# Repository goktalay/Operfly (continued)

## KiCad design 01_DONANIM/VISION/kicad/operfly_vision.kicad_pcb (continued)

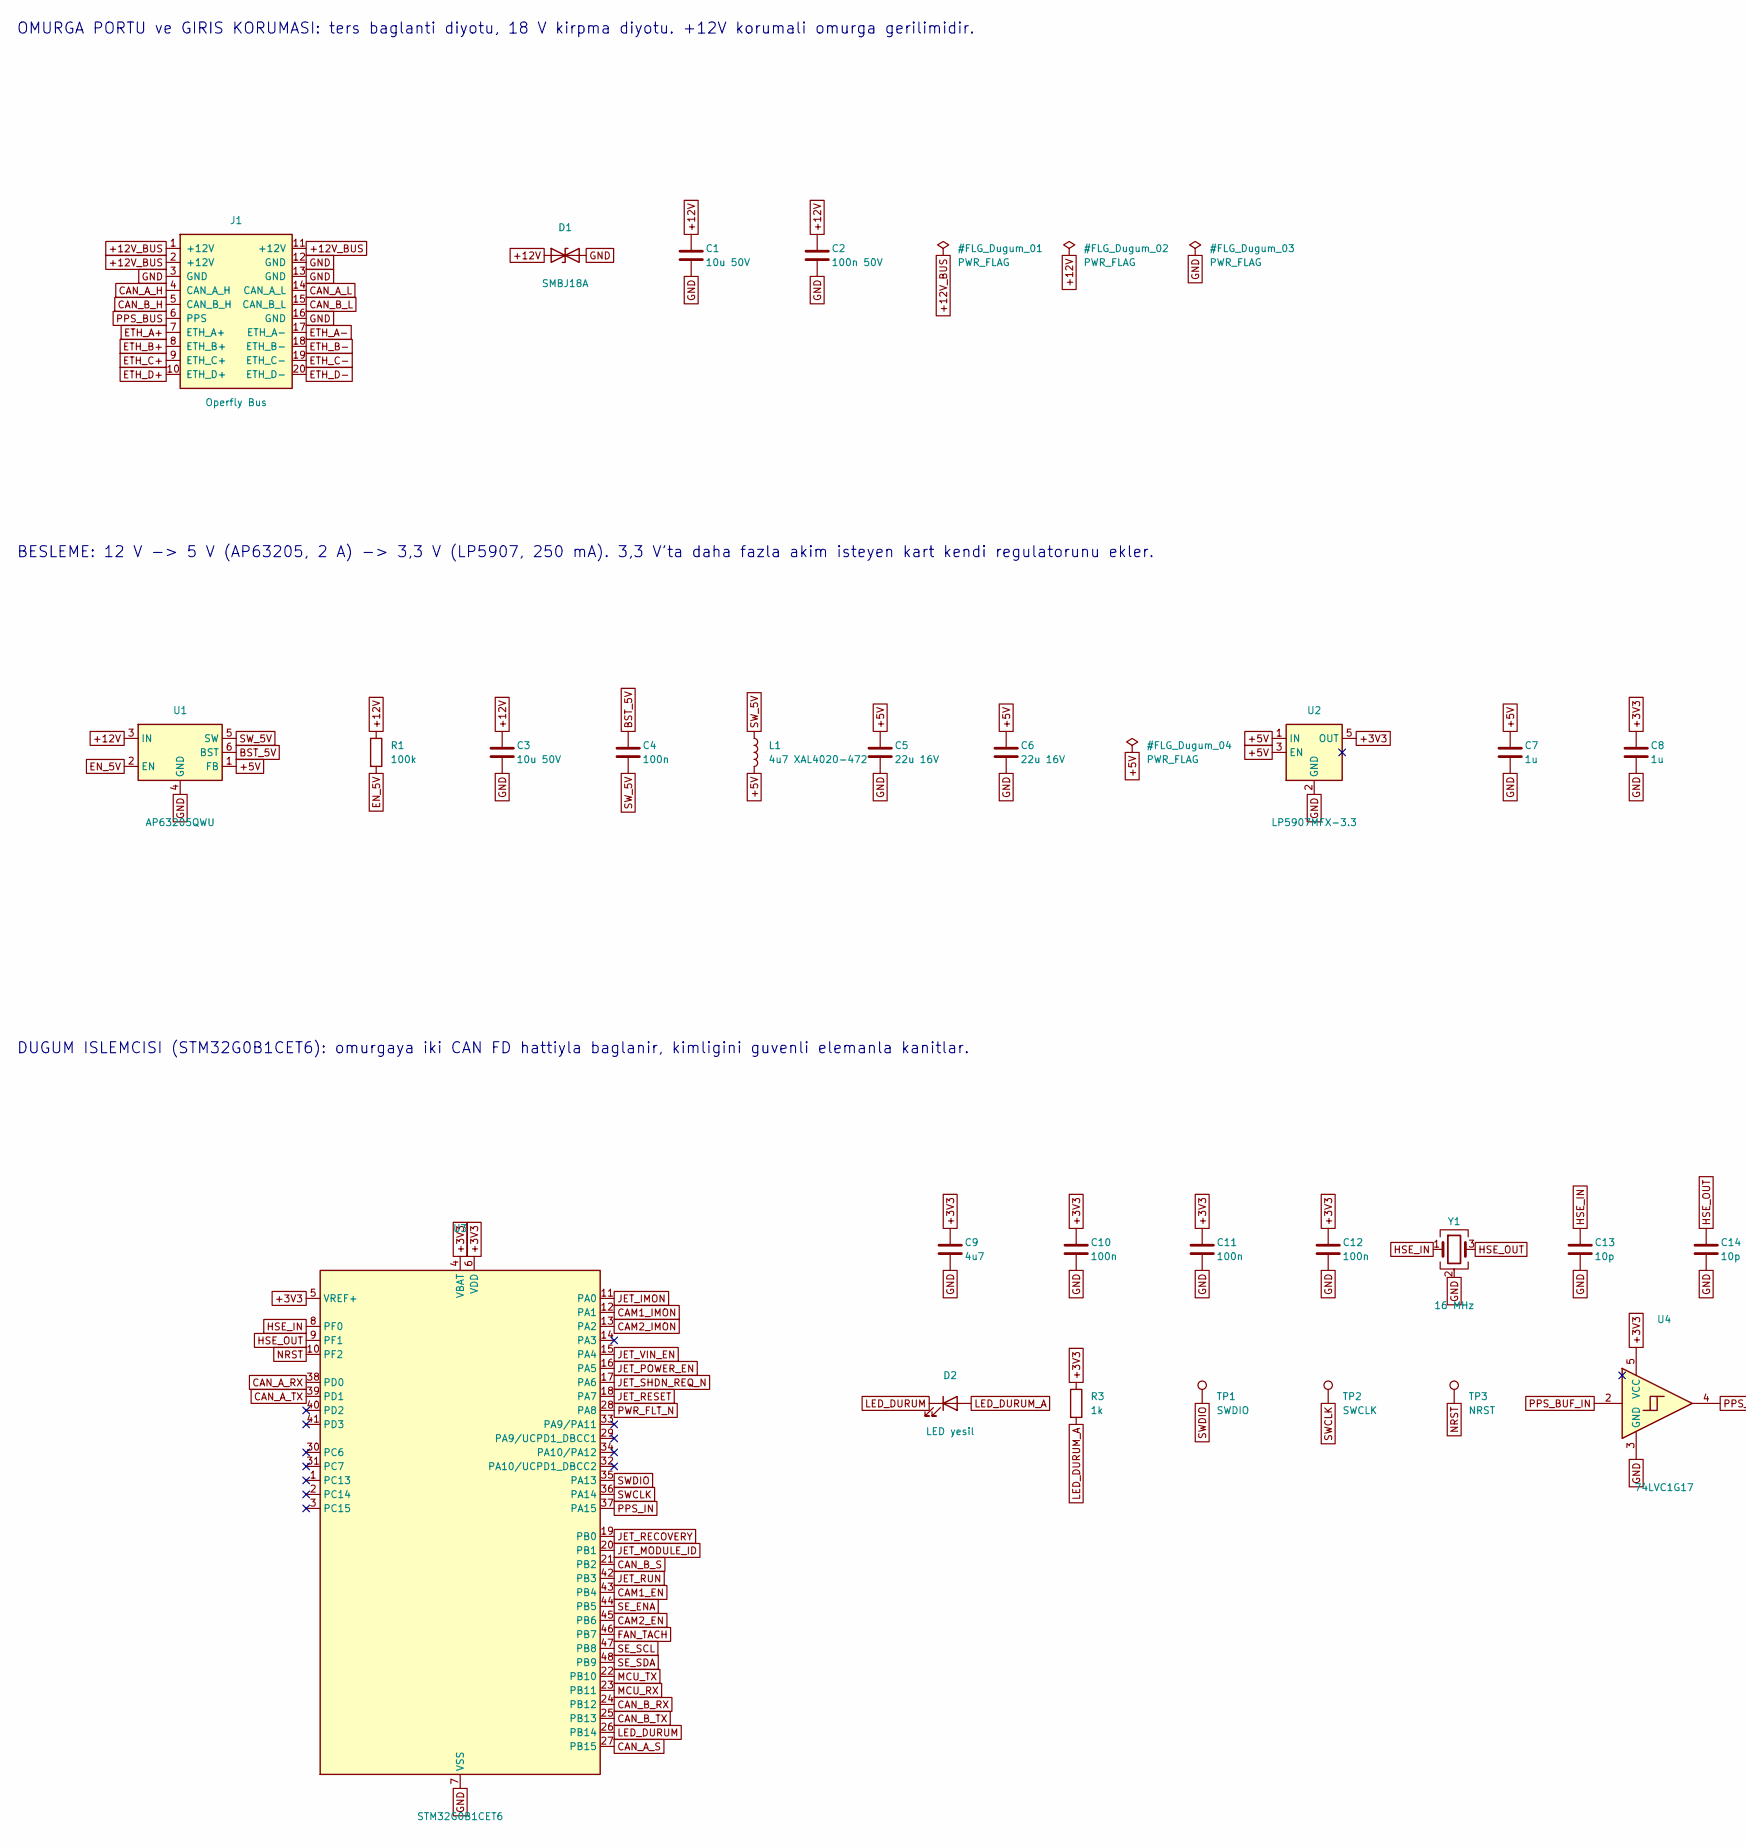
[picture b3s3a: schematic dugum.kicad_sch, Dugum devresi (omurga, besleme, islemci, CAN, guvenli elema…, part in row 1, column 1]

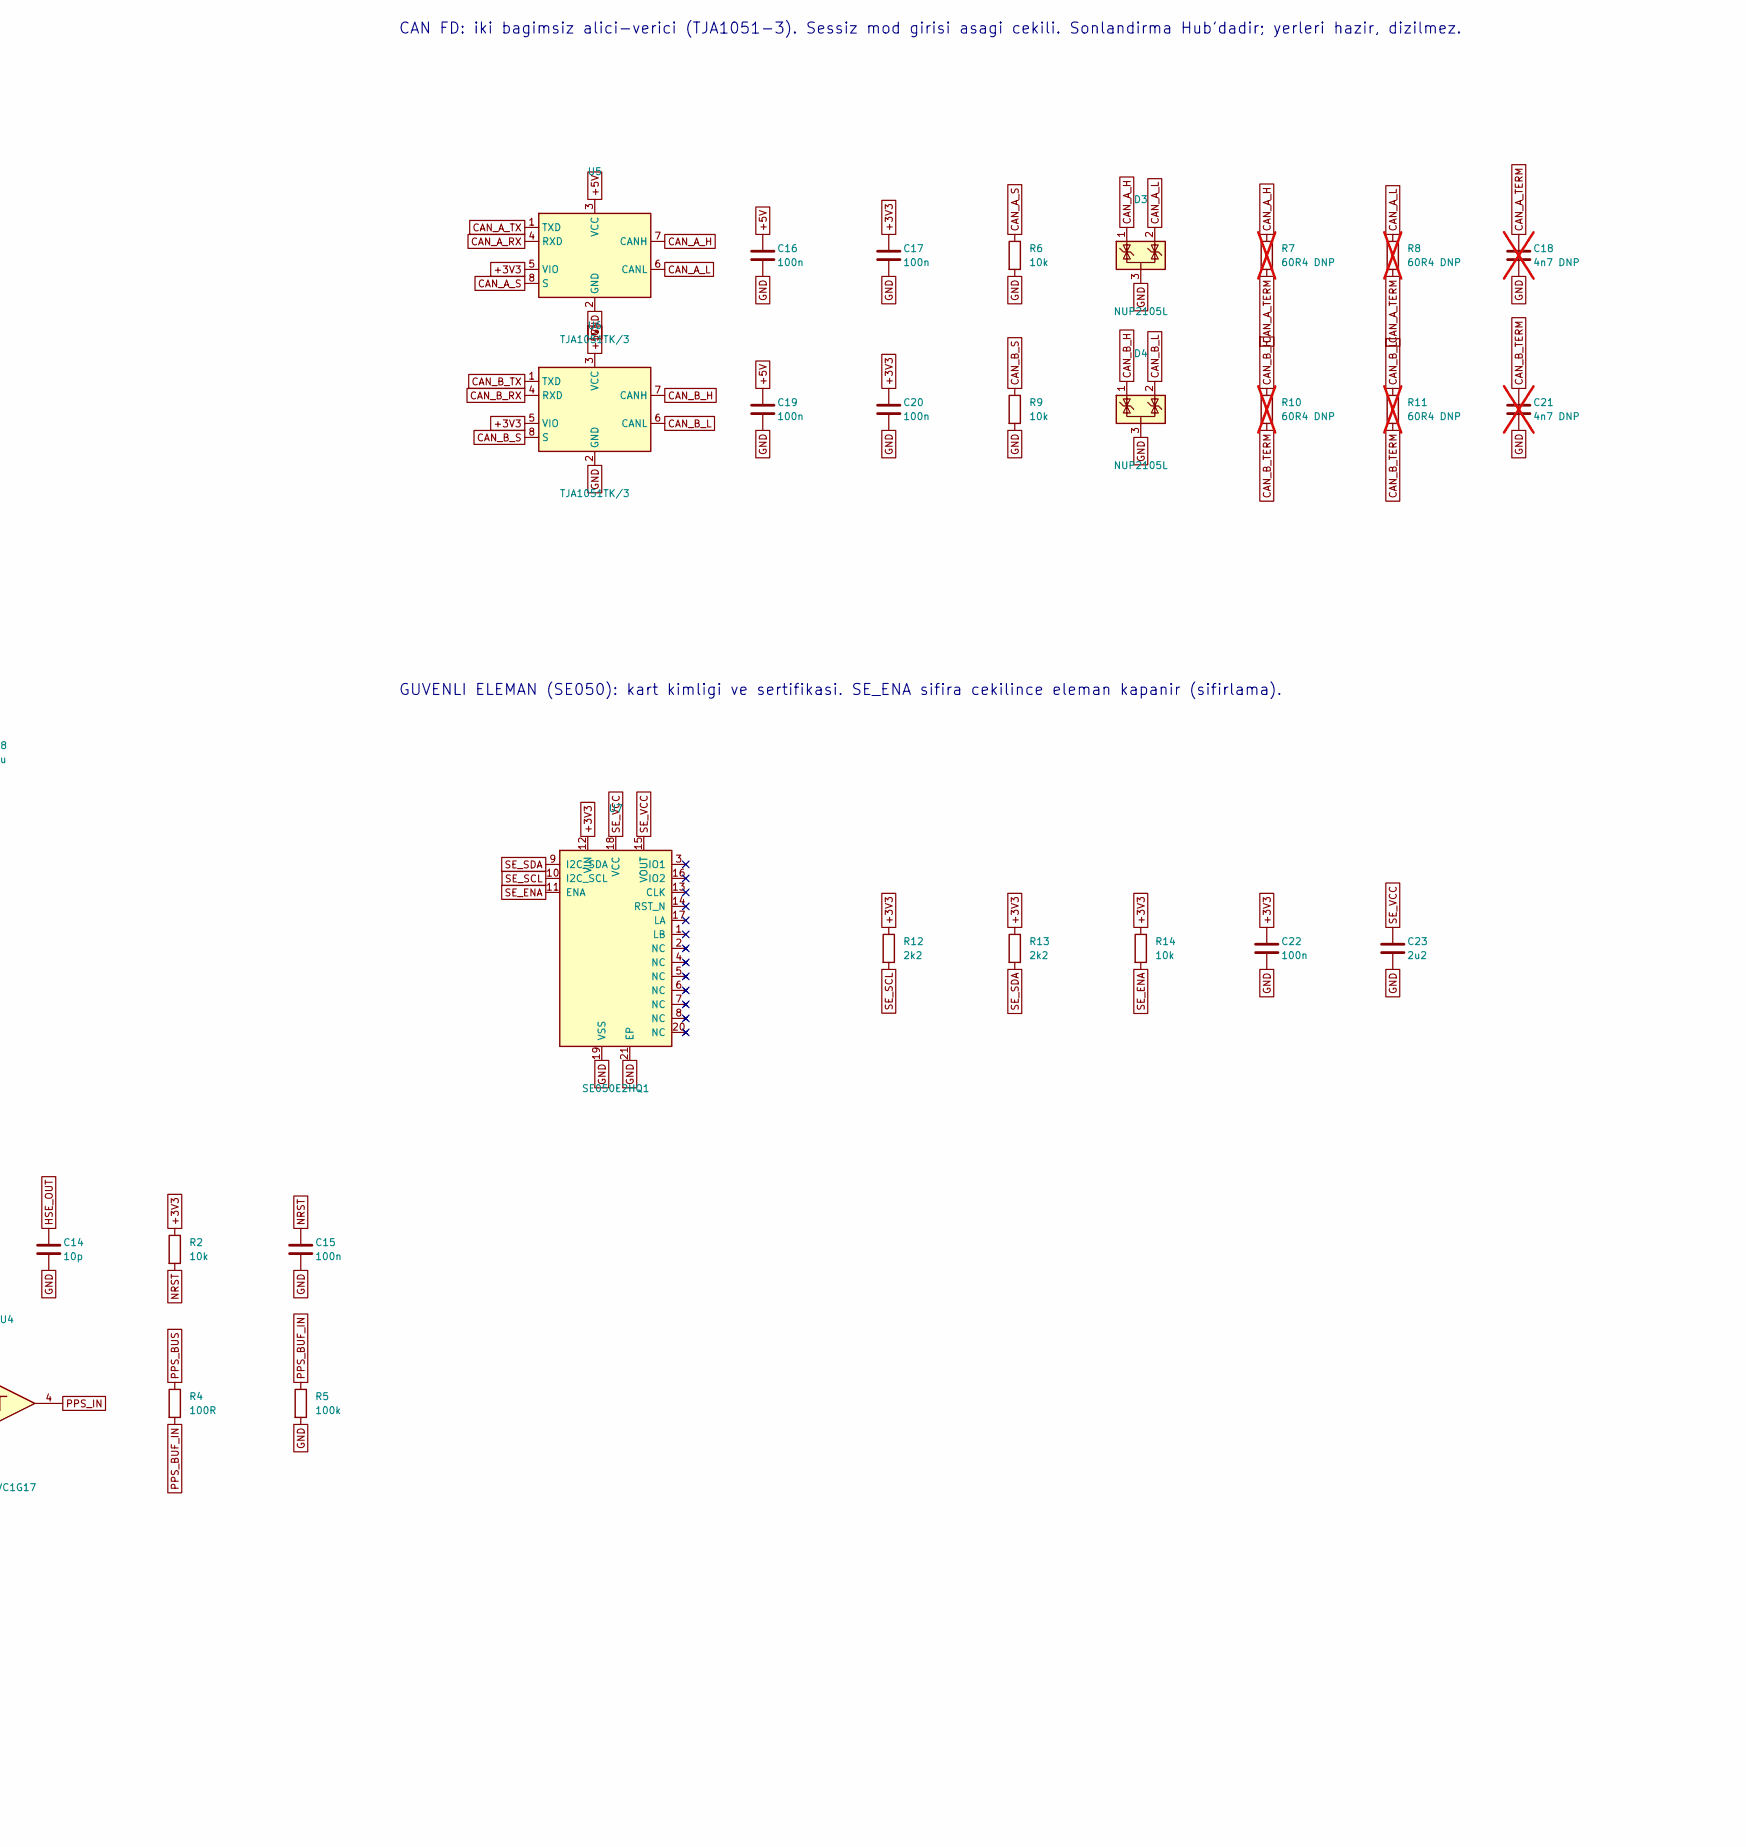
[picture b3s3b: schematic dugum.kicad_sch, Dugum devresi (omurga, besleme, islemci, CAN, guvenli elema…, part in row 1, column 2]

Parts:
C1, C3: 10u 50V; C_1206_3216Metric
C2: 100n 50V; C_0603_1608Metric
C4, C10, C11, C12, C15, C16, C17, C19, C20, C22: 100n; C_0402_1005Metric
C5, C6: 22u 16V; C_1206_3216Metric
C7, C8: 1u; C_0402_1005Metric
C9: 4u7; C_0603_1608Metric
C13, C14: 10p; C_0402_1005Metric
C18, C21: 4n7 DNP; C_0402_1005Metric; not fitted
C23: 2u2; C_0603_1608Metric
D1: SMBJ18A; D_SMB
D2: LED yesil; LED_0603_1608Metric
D3, D4: NUP2105L; SOT-23
J1: Operfly Bus; Harwin_Gecko_G125-MS12005M2P_2x10_P1.25mm_Vertical
L1: 4u7 XAL4020-472; L_Coilcraft_XAL4020-XXX
R1, R5: 100k; R_0402_1005Metric
R2, R6, R9, R14: 10k; R_0402_1005Metric
R3: 1k; R_0402_1005Metric
R4: 100R; R_0402_1005Metric
R7, R8, R10, R11: 60R4 DNP; R_0402_1005Metric; not fitted
R12, R13: 2k2; R_0402_1005Metric
TP1: SWDIO; TestPoint_Pad_D1.0mm
TP2: SWCLK; TestPoint_Pad_D1.0mm
TP3: NRST; TestPoint_Pad_D1.0mm
U1: AP63205QWU; TSOT-23-6
U2: LP5907MFX-3.3; SOT-23-5
U3: STM32G0B1CET6; LQFP-48_7x7mm_P0.5mm
U4: 74LVC1G17; SOT-353_SC-70-5
U5, U6: TJA1051TK/3; HVSON-8-1EP_3x3mm_P0.65mm_EP1.6x2.4mm
U7: SE050E2HQ1; QFN-20-1EP_3x3mm_P0.4mm_EP1.65x1.65mm
Y1: 16 MHz; Crystal_SMD_3225-4Pin_3.2x2.5mm

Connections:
+3V3: C8.1, C9.1, C10.1, C11.1, C12.1, C17.1, C20.1, C22.1, R2.1, R3.1, R12.1, R13.1, R14.1, U2.5 (OUT), U3.4 (VBAT), U3.5 (VREF+), U3.6 (VDD), U4.5 (VCC), U5.5 (VIO), U6.5 (VIO), U7.12 (VIN); also elsewhere on the board
+5V: C5.1, C6.1, C7.1, C16.1, C19.1, L1.2, U1.1 (FB), U2.1 (IN), U2.3 (EN), U5.3 (VCC), U6.3 (VCC); also elsewhere on the board
+12V: C1.1, C2.1, C3.1, D1.1 (A1), R1.1, U1.3 (IN); also elsewhere on the board
+12V_BUS: J1.1 (+12V), J1.2 (+12V), J1.11 (+12V); also elsewhere on the board
BST_5V: C4.1, U1.6 (BST)
CAM1_EN: U3.43 (PB4); also elsewhere on the board
CAM1_IMON: U3.12 (PA1); also elsewhere on the board
CAM2_EN: U3.45 (PB6); also elsewhere on the board
CAM2_IMON: U3.13 (PA2); also elsewhere on the board
CAN_A_H: D3.1 (K), J1.4 (CAN_A_H), R7.1, U5.7 (CANH)
CAN_A_L: D3.2 (K), J1.14 (CAN_A_L), R8.1, U5.6 (CANL)
CAN_A_RX: U3.38 (PD0), U5.4 (RXD)
CAN_A_S: R6.1, U3.27 (PB15), U5.8 (S)
CAN_A_TERM: C18.1, R7.2, R8.2
CAN_A_TX: U3.39 (PD1), U5.1 (TXD)
CAN_B_H: D4.1 (K), J1.5 (CAN_B_H), R10.1, U6.7 (CANH)
CAN_B_L: D4.2 (K), J1.15 (CAN_B_L), R11.1, U6.6 (CANL)
CAN_B_RX: U3.24 (PB12), U6.4 (RXD)
CAN_B_S: R9.1, U3.21 (PB2), U6.8 (S)
CAN_B_TERM: C21.1, R10.2, R11.2
CAN_B_TX: U3.25 (PB13), U6.1 (TXD)
EN_5V: R1.2, U1.2 (EN)
ETH_A+: J1.7 (ETH_A+); also elsewhere on the board
ETH_A-: J1.17 (ETH_A-); also elsewhere on the board
ETH_B+: J1.8 (ETH_B+); also elsewhere on the board
ETH_B-: J1.18 (ETH_B-); also elsewhere on the board
ETH_C+: J1.9 (ETH_C+); also elsewhere on the board
ETH_C-: J1.19 (ETH_C-); also elsewhere on the board
ETH_D+: J1.10 (ETH_D+); also elsewhere on the board
ETH_D-: J1.20 (ETH_D-); also elsewhere on the board
FAN_TACH: U3.46 (PB7); also elsewhere on the board
GND: C1.2, C2.2, C3.2, C5.2, C6.2, C7.2, C8.2, C9.2, C10.2, C11.2, C12.2, C13.2, C14.2, C15.2, C16.2, C17.2, C18.2, C19.2, C20.2, C21.2, C22.2, C23.2, D1.2 (A2), D3.3 (A), D4.3 (A), J1.3 (GND), J1.12 (GND), J1.13 (GND), J1.16 (GND), R5.2, R6.2, R9.2, U1.4 (GND), U2.2 (GND), U3.7 (VSS), U4.3 (GND), U5.2 (GND), U5.9 (GND), U6.2 (GND), U6.9 (GND), U7.19 (VSS), U7.21 (EP), Y1.2 (G), Y1.4 (G); also elsewhere on the board
HSE_IN: C13.1, U3.8 (PF0), Y1.1
HSE_OUT: C14.1, U3.9 (PF1), Y1.3
JET_IMON: U3.11 (PA0); also elsewhere on the board
JET_MODULE_ID: U3.20 (PB1); also elsewhere on the board
JET_POWER_EN: U3.16 (PA5); also elsewhere on the board
JET_RECOVERY: U3.19 (PB0); also elsewhere on the board
JET_RESET: U3.18 (PA7); also elsewhere on the board
JET_RUN: U3.42 (PB3); also elsewhere on the board
JET_SHDN_REQ_N: U3.17 (PA6); also elsewhere on the board
JET_VIN_EN: U3.15 (PA4); also elsewhere on the board
LED_DURUM: D2.1 (K), U3.26 (PB14)
LED_DURUM_A: D2.2 (A), R3.2
MCU_RX: U3.23 (PB11); also elsewhere on the board
MCU_TX: U3.22 (PB10); also elsewhere on the board
NRST: C15.1, R2.2, TP3.1, U3.10 (PF2)
PPS_BUF_IN: R4.2, R5.1, U4.2
PPS_BUS: J1.6 (PPS), R4.1
PPS_IN: U3.37 (PA15), U4.4; also elsewhere on the board
PWR_FLT_N: U3.28 (PA8); also elsewhere on the board
SE_ENA: R14.2, U3.44 (PB5), U7.11 (ENA)
SE_SCL: R12.2, U3.47 (PB8), U7.10 (I2C_SCL)
SE_SDA: R13.2, U3.48 (PB9), U7.9 (I2C_SDA)
SE_VCC: C23.1, U7.15 (VOUT), U7.18 (VCC)
SWCLK: TP2.1, U3.36 (PA14)
SWDIO: TP1.1, U3.35 (PA13)
SW_5V: C4.2, L1.1, U1.5 (SW)

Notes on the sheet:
DUGUM ISLEMCISI (STM32G0B1CET6): omurgaya iki CAN FD hattiyla baglanir, kimligini guvenli elemanla kanitlar.
BESLEME: 12 V -> 5 V (AP63205, 2 A) -> 3,3 V (LP5907, 250 mA). 3,3 V'ta daha fazla akim isteyen kart kendi regulatorunu ekler.
CAN FD: iki bagimsiz alici-verici (TJA1051-3). Sessiz mod girisi asagi cekili. Sonlandirma Hub'dadir; yerleri hazir, dizilmez.
GUVENLI ELEMAN (SE050): kart kimligi ve sertifikasi. SE_ENA sifira cekilince eleman kapanir (sifirlama).
OMURGA PORTU ve GIRIS KORUMASI: ters baglanti diyotu, 18 V kirpma diyotu. +12V korumali omurga gerilimidir.
